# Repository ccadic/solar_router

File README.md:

This is a first POC of solar router
No doc at the moment.
GPL 3 licence

If you want to reward, my BTC wallet address is: bc1qpzu36plm902ja7kxqkrrrryu32tg3zaknm2wsk
Have fun , @sulfuroid

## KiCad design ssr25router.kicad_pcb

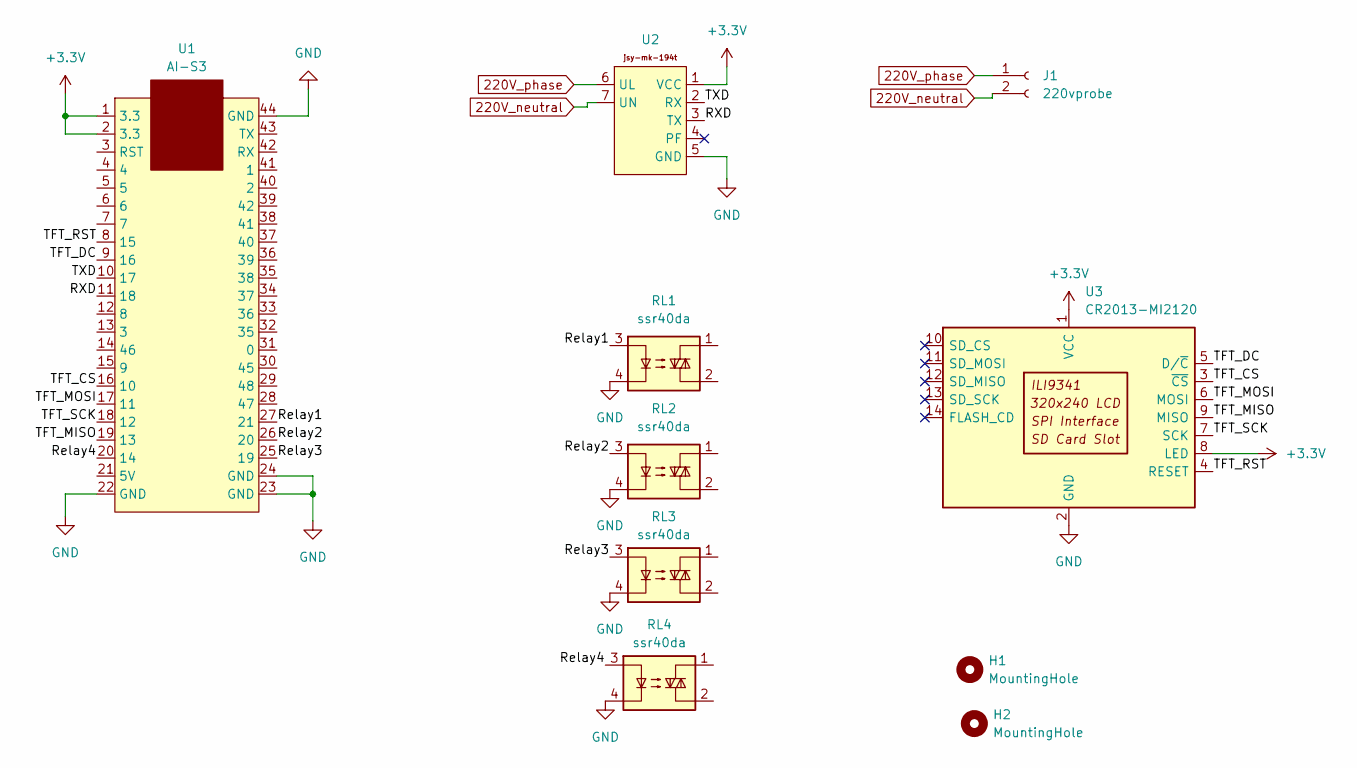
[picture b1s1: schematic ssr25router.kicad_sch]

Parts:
H1, H2: MountingHole; MountingHole_2.5mm_Pad_Via
J1: 220vprobe; 220VCNX
RL1, RL2, RL3, RL4: ssr40da; SSR40DA
U1: AI-S3
U2: JSY-mk-194tpcb
U3: CR2013-MI2120

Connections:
220V_neutral: J1.2, U2.7 (UN)
220V_phase: J1.1, U2.6 (UL)
+3.3V: U1.1 (3.3), U1.2 (3.3), U2.1 (VCC), U3.1 (VCC), U3.8 (LED)
/RXD: U1.11 (18), U2.3 (TX)
/Relay1: RL1.3, U1.27 (21)
/Relay2: RL2.3, U1.26 (20)
/Relay3: RL3.3, U1.25 (19)
/Relay4: RL4.3, U1.20 (14)
/TFT_CS: U1.16 (10), U3.3 (~CS)
/TFT_DC: U1.9 (16), U3.5 (D/~C)
/TFT_MISO: U1.19 (13), U3.9 (MISO)
/TFT_MOSI: U1.17 (11), U3.6 (MOSI)
/TFT_RST: U1.8 (15), U3.4 (RESET)
/TFT_SCK: U1.18 (12), U3.7 (SCK)
/TXD: U1.10 (17), U2.2 (RX)
GND: RL1.4, RL2.4, RL3.4, RL4.4, U1.22 (GND), U1.23 (GND), U1.24 (GND), U1.44 (GND), U2.5 (GND), U3.2 (GND)

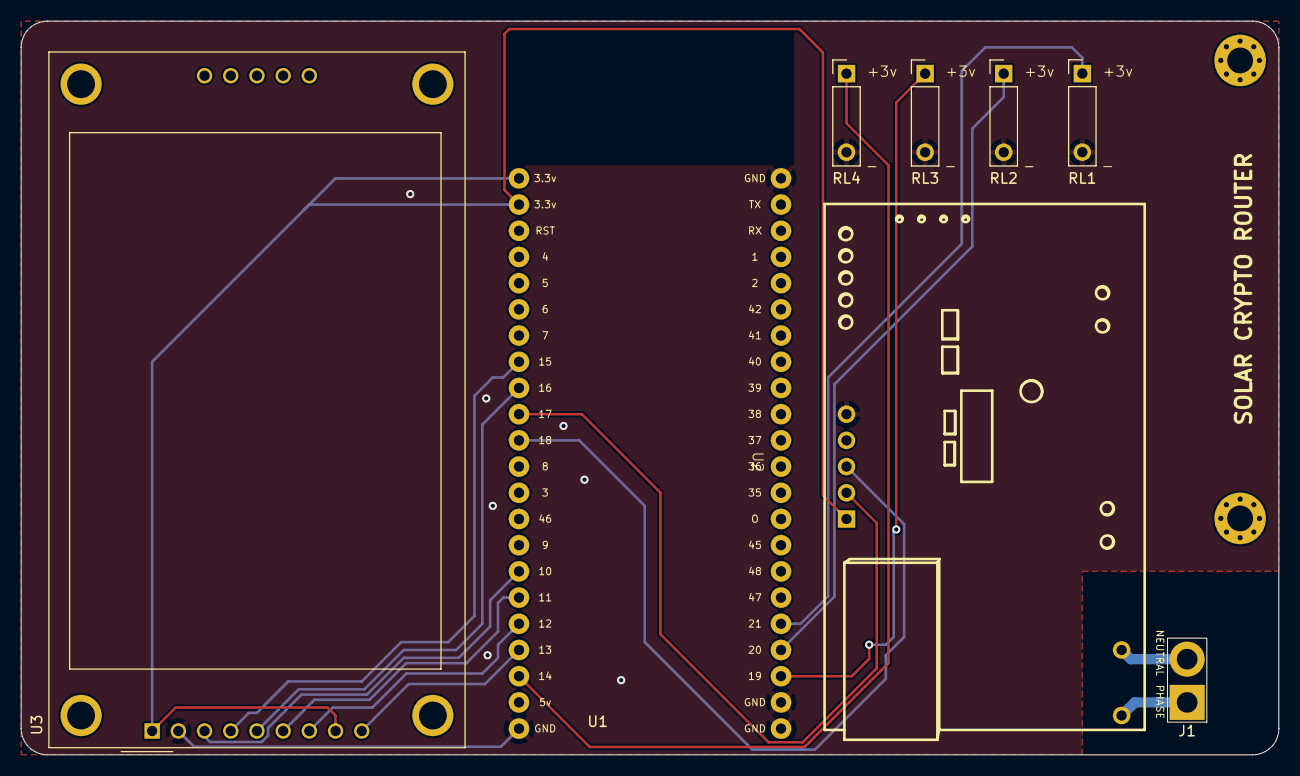
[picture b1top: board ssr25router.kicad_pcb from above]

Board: 2 copper layers, 121.9 x 71.1 mm, 10 parts (0 on the bottom side), 16 nets.
